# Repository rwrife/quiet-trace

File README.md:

# Quiet Trace

> USB-powered ESP32-S3 ambient sound-level logger for home offices and shared rooms that keeps only privacy-preserving loudness summaries and serves a local history dashboard—never raw audio.

## Overview

Quiet Trace is an open-hardware instrument for understanding *when* a room becomes noisy without installing a recorder or sending microphone data to a cloud service. An ESP32-S3 samples a digital MEMS microphone, calculates bounded-window loudness statistics in memory, discards each audio buffer, and stores only aggregate records such as one-minute equivalent level, peak window, and histogram buckets. A responsive dashboard served on the local network shows live level, timelines, annotations, and portable exports.

Quiet Trace is a practical survey and awareness tool, **not** a certified sound-level meter, occupational exposure instrument, medical device, security monitor, or legal evidence recorder. Displayed units must be labeled uncalibrated until the device has completed a documented reference-meter calibration.

## Motivation

Phone sound-meter apps are convenient but tie up a phone, vary by device, and can create understandable recording concerns. Professional logging meters are expensive and often export through proprietary software. Quiet Trace aims for a small, repairable, visibly non-recording device that can remain on a desk, compare rooms or time periods, and keep the data owner in control.

## Target users

- Remote workers comparing distracting periods before changing their schedule or workspace.
- Households investigating recurring appliance, traffic, or shared-room noise patterns.
- Makers learning digital audio measurement, calibration, embedded aggregation, and privacy-by-design.
- Community rooms and workshops that want a simple local trend display without storing conversations.

## Concrete use cases

1. Put Quiet Trace on a desk, select an existing room label, and watch the current aggregate level.
2. Add a local annotation such as “window opened” or “dishwasher started” and compare the before/after timeline.
3. Move the device to another room and run the same timed survey profile.
4. Export versioned CSV/JSON summaries for a spreadsheet, then delete selected sessions from the device.
5. Demonstrate privacy by inspecting the firmware/data schema: no waveform, encoded audio, transcript, or frequency reconstruction data is persisted or sent.

## Intended workflow

1. Connect Quiet Trace to a certified USB 5 V supply or computer.
2. On first setup, hold the physical setup button to open a time-limited local setup session.
3. Join the temporary device network or use USB serial, set a device name/time source, and optionally provide local Wi-Fi credentials.
4. Open the device-hosted dashboard from a phone or computer on the same network.
5. Choose a room/session label and start logging. The LED communicates recording-*statistics* state without relying on color alone.
6. Review live and historical aggregates; annotate, export, back up, or erase them locally.
7. If calibrated readings are needed, follow the reference-meter procedure and retain the calibration date and offset with every export.

If Wi-Fi is unavailable, logging and physical status remain functional; USB serial supports configuration and data export. No internet service or account is required.

## MVP features

- ESP32-S3 controller, digital I2S/PDM MEMS microphone, status LED, setup/mark button, USB power/data, and test points on an editable KiCad carrier board.
- Fixed-size in-memory sample buffers, documented weighting/aggregation math, and irreversible raw-sample discard.
- One-minute summary records with monotonic sequence, wall-clock quality flag, average/equivalent level, bounded peak, and histogram buckets.
- Explicit calibration state: uncalibrated by default; single-point offset procedure against a reference meter.
- Local flash ring buffer with wear-aware commits and export-before-erase controls.
- Device-hosted responsive web dashboard for setup, live status, history, annotations, CSV/JSON export, backup/restore, retention, and deletion.
- Local-only authenticated API and time-limited physical-presence setup mode.
- Repeatable firmware/web builds, simulation or hardware-abstraction tests, ERC/DRC evidence, bring-up measurements, and assembly/fabrication documentation.

## Non-goals

- Persisting or streaming raw audio, audio clips, spectra, voice activity, speech, transcripts, or speaker identity.
- Certified IEC/ANSI sound-level measurements, occupational dose, hearing-risk advice, diagnosis, treatment, emergency alerts, or regulatory compliance.
- Remote surveillance, cloud dashboards, accounts, analytics, advertisements, or subscription services.
- Automatic identification of a sound source.
- Battery charging in the MVP; operation is USB 5 V SELV only.

## Privacy, permissions, and data storage

Raw microphone samples exist only in bounded RAM buffers required for calculation and are overwritten after each window. The device must never write or transmit samples, recordings, transcripts, or reconstructable spectral data. Stored records contain aggregates, device/session metadata, user-entered annotations, calibration metadata, and timestamps. Data stays in on-device flash and the browser’s local storage unless the user explicitly downloads an export.

The dashboard requires local-network access. Wi-Fi credentials are stored only on the device, must be erasable by a physical reset flow, and are never included in ordinary exports. Setup credentials/tokens must not be hard-coded. No microphone permission is requested from the phone or computer because the device owns the sensor. Optional browser file access is user-initiated for backup restore only.

## Hardware direction

Revision A selects an Espressif `ESP32-S3-WROOM-1-N8R8` module and TDK InvenSense `ICS-43434` I²S microphone, with USB-C 5 V power/protection, non-color-only LED status, physical RESET and SETUP/MARK controls, recovery header, and test access. Exact selected parts, pin/package checks, acoustic constraints, the LDO thermal bound, and point-in-time sourcing evidence are documented in [hardware/parts-selection.md](hardware/parts-selection.md). Stock, prices, and formal lifecycle status still require a pre-order procurement check.

Current editable sources are:

```text
hardware/kicad/quiet-trace.kicad_pro
hardware/kicad/quiet-trace.kicad_sch
hardware/kicad/quiet-trace.kicad_pcb
```

PDFs and renders may supplement these files but will never replace them. Final BOM data lives in KiCad schematic symbol properties (`Manufacturer`, `MPN`, supplier fields, and notes) and is exported to tracked [`bom/bom.csv`](bom/bom.csv). `bom/preliminary-bom.csv` remains planning input only.

Prototype planning target: **USD 35–60**, including electronics, simple enclosure, cable, and ordinary fasteners but excluding a phone/computer, tools, and a reference sound meter. This is a target rather than a live quote; the tracked BOM preserves `TBD` wherever current unit pricing was not actually observed, and all availability must be rechecked before ordering.

## Safety limits

- USB 5 V SELV only; no mains wiring, battery charging, or control of safety-critical equipment.
- Use a certified USB supply and intact cable.
- Indoor, dry-location prototype; not weatherproof.
- Enclosure must prevent conductive debris contact while preserving the microphone’s specified acoustic path.
- Results are informational and unfit for hearing-safety, workplace compliance, tenancy disputes, law enforcement, or emergency decisions.

## Current status and milestones

**Status: issue-5 dashboard/protocol slice is merged; issue-6 physical integration evidence is in progress.** The repository now contains architecture/privacy/metric contracts, selected schematic/BOM, PCB/mechanical draft, host-tested firmware domain contracts, and the merged local dashboard implementation with typed aggregate protocol fixtures. Issue #6 assembly/bring-up/calibration/troubleshooting guides are published, but real bench measurements and end-to-end physical evidence are still required before any calibrated claim. No certification, safety, legal, or bench-calibrated claim is made.

1. Freeze measurable requirements and privacy threat model.
2. Validate controller/microphone/protection choices from manufacturer datasheets.
3. Create the real KiCad schematic and schematic-backed BOM; pass ERC.
4. Build the aggregation firmware and local dashboard against synthetic fixtures.
5. Lay out the PCB; pass DRC and KiCad analysis.
6. Integrate and bring up a prototype with documented measurements and calibration limits.
7. Publish assembly instructions and inspected fabrication/release outputs.

See [PLAN.md](PLAN.md), [hardware/requirements.md](hardware/requirements.md), and the GitHub issue backlog.

Issue-#6 integration documents:
- [Assembly guide](docs/integration/assembly-guide.md)
- [Bring-up checklist](docs/integration/bring-up-checklist.md)
- [Calibration/reference comparison procedure](docs/integration/calibration-reference-comparison.md)
- [Troubleshooting guide](docs/integration/troubleshooting.md)
- [Bench evidence log template](docs/integration/bench-log-template.md)

## Development quickstart

Pinned versions and setup details are in [docs/toolchains.md](docs/toolchains.md).

```bash
# Dashboard: exact lockfile, static checks, tests, and production bundle
cd app
npm ci
npm run format:check
npm run lint
npm run typecheck
npm run test:run
npm run build

# Host-testable firmware domain contract
cd ..
cmake -S firmware/host_tests -B /tmp/quiet-trace-host-tests \
  -DCMAKE_BUILD_TYPE=Release
cmake --build /tmp/quiet-trace-host-tests --parallel
ctest --test-dir /tmp/quiet-trace-host-tests --output-on-failure

# ESP-IDF v6.1 target scaffold (after exporting the pinned IDF environment)
cd firmware
idf.py set-target esp32s3
idf.py build
```

The dashboard’s synthetic view is opt-in at `/?fixture=1` and visibly marked as fixture-only. The default route does not fabricate sensor data. Target flashing, microphone behavior, calibration, and bench results remain unverified until the exact hardware is selected and present.

## Licensing plan

The initial documentation/software scaffold is MIT licensed. Before hardware source release, the project will add an explicit open-hardware license (planned CERN-OHL-S-2.0) and document boundaries for firmware, web app, documentation, and third-party assets.

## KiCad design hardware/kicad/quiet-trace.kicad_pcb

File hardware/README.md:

# Quiet Trace hardware

## System block description

```text
USB-C 5 V SELV
      │
      ├─ input protection / regulated module rail / test points
      │
      ▼
ESP32-S3 module ── digital audio ── MEMS microphone + acoustic port
      │
      ├─ setup/mark button
      ├─ status LED with blink-pattern redundancy
      ├─ native USB / serial recovery
      └─ Wi-Fi local dashboard
```

The first revision is a carrier around an Espressif ESP32-S3 module rather than a chip-down RF design. It should remain hand-assemblable, expose recovery and measurement points, and keep the module antenna region outside copper/enclosure obstructions.

## Controller choice

Revision A selects `ESP32-S3-WROOM-1-N8R8` after comparison with `ESP32-S3-MINI-1-N8`. The WROOM variant provides 8 MB flash and 8 MB PSRAM, native USB on GPIO19/GPIO20, official KiCad library support, and a less dense assembly footprint. See [parts-selection.md](parts-selection.md) for datasheet citations, sourcing limits, and the +65 °C normal operating limit of the R8 PSRAM variant.

## Interfaces

- Digital microphone: TDK InvenSense `ICS-43434`, 24-bit I²S; firmware clocks must stay within the selected datasheet operating bands.
- USB: 5 V power plus flashing, logs, setup, recovery, and aggregate export.
- Wi-Fi: local HTTP/JSON/SSE only; internet not required.
- Human input: one setup/mark button with short/long press semantics.
- Human output: LED patterns that remain understandable without color perception.
- Debug/test: ground, input/regulated rail, reset/boot, audio clocks/data, and spare serial/SWD-style module test access as supported.

## Power plan

USB 5 V SELV only. Revision A uses a 500 mA-hold resettable fuse, VBUS TVS, USB data ESD array, and a 600 mA AP2112K 3.3 V LDO. The LDO's current rating is not continuous thermal capacity: [parts-selection.md](parts-selection.md) records the static thermal bounds and required worst-case current/temperature bring-up measurement. No battery, charging circuit, mains interface, PoE, or external actuator is in MVP. Use a certified USB supply and intact cable.

## Revision-A PCB and enclosure

Revision A uses an 80 × 52 mm two-layer carrier with four M3 holes. The USB-C receptacle is on the left edge, the WROOM module antenna overhangs the top edge, the bottom-port microphone is aligned to its footprint's 0.5 mm NPTH, and reset/setup/status controls remain accessible from the top. The board has labeled test points for protected 5 V, 3V3, GND, USB D+/D−, microphone clocks/data, EN, and BOOT0.

`hardware/mechanical/quiet-trace-enclosure.scad` is an editable 88 × 60 × 24 mm two-part enclosure model. It aligns standoffs, USB access, button holes, status window, and microphone opening to PCB coordinates and opens with common M3 hardware. The model is dimensional/static evidence only: it has not been printed, assembled, RF-tested, thermally tested, or acoustically characterized.

## Safety limits

- Indoor dry-location prototype, USB 5 V SELV only.
- No claim of ingress protection, acoustic certification, hearing safety, regulatory compliance, surveillance, or emergency monitoring.
- Keep conductive debris away and maintain the module antenna/microphone keepouts.
- Raw audio must never be persisted or transmitted.

## Expected KiCad deliverables

Current editable paths:

```text
hardware/kicad/quiet-trace.kicad_pro
hardware/kicad/quiet-trace.kicad_sch
hardware/kicad/quiet-trace.kicad_pcb
hardware/kicad/quiet-trace.kicad_dru
hardware/mechanical/quiet-trace-enclosure.scad
```

The design must include power/protection, controller/module sockets or pads, microphone interface, controls, status, programming/recovery, test points, mounting, antenna/acoustic keepouts, and labeled connectors. Completion requires actual ERC/DRC output with every exception resolved or documented. Renders and schematic PDFs supplement but do not replace editable KiCad source.

Layout implementation: the official ESP32-S3-WROOM-1 footprint's embedded F.Cu/B.Cu antenna rule area spans the radiating edge and forbids tracks, vias, pads, pours, and footprints. U4 retains the footprint's 0.5 mm acoustic NPTH; board-level front/back acoustic rule areas prevent pours/vias beneath it and prevent back-side tracks. U3 sits directly behind J1; R3/R4 terminate near U1; C1/C2 flank U2; C3/C4 sit at the module rail entry; C5 is adjacent to U4. J2 remains DNP by default.

The continuous-ground strategy uses filled GND zones on F.Cu and B.Cu, clipped by antenna, mounting, and microphone rule areas. Power nets are widened after routing (`VBUS_RAW`/`USB_5V` 0.4 mm, `+3V3` 0.5 mm); USB and I²S are 0.25 mm. The custom rule file enforces these widths/clearances. These dimensions support a conservative two-layer prototype; they do not constitute controlled-impedance or EMC-compliance evidence.

### Assembly/fabrication constraints

- Two-layer 1.6 mm FR-4, 1 oz copper planning basis; minimum track/clearance 0.2 mm, minimum copper-to-edge 0.5 mm.
- Keep all copper, components, metal hardware, conductive coating, and cabling out of the WROOM antenna rule area.
- Do not apply solder paste, wash fluid, mesh, foam, adhesive, or debris to the ICS-43434 sound hole. Align any enclosure port before assembly.
- Fit U3 directly behind J1 and inspect USB-C/ESD orientation before power. D2 is bidirectional; D1 polarity and all IC/module pin-1 marks are present in the library footprints/silkscreen.
- J2 is DNP unless needed for development. Preserve access to U2 and TP1/TP2/TP3 for issue-#6 rail/current/temperature measurements.
- No Gerber/CPL/release package is checked in at this stage; issue #7 owns final fabrication export and inspection.

The reproducible issue-#2 ERC/netlist/BOM evidence is recorded in [`docs/verification/issue-2-schematic.md`](../docs/verification/issue-2-schematic.md). Issue-#3 DRC, routing, cross-analysis, EMC/thermal triage, and mechanical evidence is recorded in [`docs/verification/issue-3-pcb-mechanical.md`](../docs/verification/issue-3-pcb-mechanical.md). Issue-#6 integration docs are in [`docs/integration/assembly-guide.md`](../docs/integration/assembly-guide.md), [`docs/integration/bring-up-checklist.md`](../docs/integration/bring-up-checklist.md), [`docs/integration/calibration-reference-comparison.md`](../docs/integration/calibration-reference-comparison.md), and [`docs/integration/troubleshooting.md`](../docs/integration/troubleshooting.md), with run-time capture template [`docs/integration/bench-log-template.md`](../docs/integration/bench-log-template.md). After exporting the KiCad XML netlist, run `python3 hardware/kicad/verify_netlist.py hardware/kicad/quiet-trace.xml` and `python3 hardware/kicad/verify_pcb.py hardware/kicad/quiet-trace.xml hardware/kicad/quiet-trace.kicad_pcb`.

Final Manufacturer/MPN/supplier data belongs in schematic symbol properties and is exported to `bom/bom.csv`; `bom/preliminary-bom.csv` is not the source of truth.

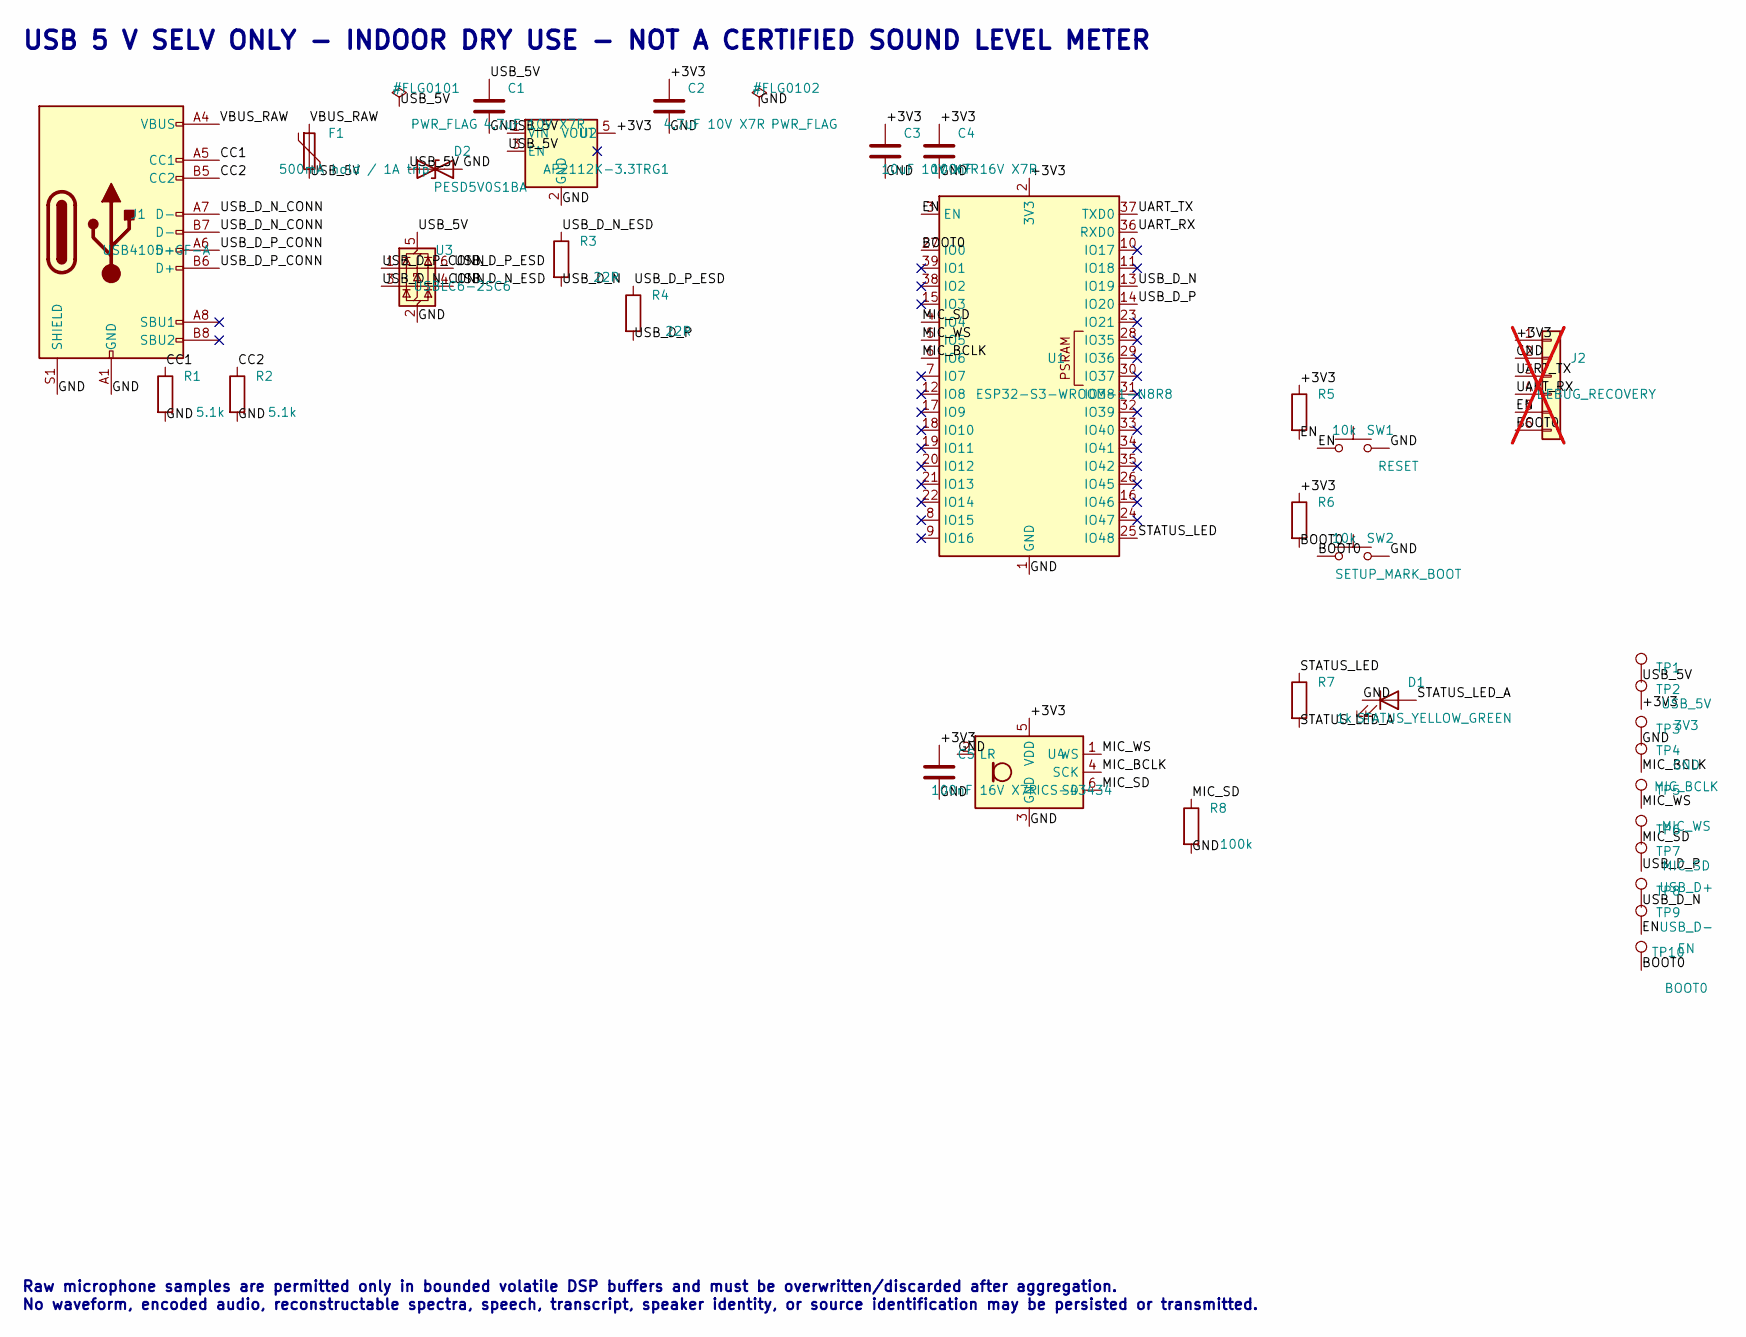
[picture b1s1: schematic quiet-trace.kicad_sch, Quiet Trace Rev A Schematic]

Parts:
C1, C2: 4.7uF 10V X7R; C_0603_1608Metric; MPN TCC0603X7R475K100CT
C3: 10uF 10V X7R; C_0805_2012Metric; MPN GRM21BR71A106KE51L
C4, C5: 100nF 16V X7R; C_0603_1608Metric; MPN GRM188R71C104KA01D
D1: STATUS_YELLOW_GREEN; LED_0805_2012Metric; MPN LTST-C170KGKT
D2: PESD5V0S1BA; D_SOD-323; MPN PESD5V0S1BA,115
F1: 500mA hold / 1A trip; Fuse_1206_3216Metric; MPN BSMD1206-050-16V
J1: USB4105-GF-A; USB_C_Receptacle_GCT_USB4105-xx-A_16P_TopMnt_Horizontal; MPN USB4105-GF-A
J2: DEBUG_RECOVERY; PinHeader_1x06_P2.54mm_Vertical; MPN M20-9990645; not fitted
R1, R2: 5.1k; R_0603_1608Metric; MPN 0603WAF5101T5E
R3, R4: 22R; R_0603_1608Metric; MPN 0603WAF220JT5E
R5, R6: 10k; R_0603_1608Metric; MPN 0603WAF1002T5E
R7: 1k; R_0603_1608Metric; MPN 0603WAF1001T5E
R8: 100k; R_0603_1608Metric; MPN 0603WAF1003T5E
SW1: RESET; SW_Push_1P1T_NO_CK_KMR2; MPN KMR221GLFS
SW2: SETUP_MARK_BOOT; SW_Push_1P1T_NO_CK_KMR2; MPN KMR221GLFS
TP1: USB_5V; TestPoint_Pad_D1.5mm; MPN N/A
TP2: 3V3; TestPoint_Pad_D1.5mm; MPN N/A
TP3: GND; TestPoint_Pad_D1.5mm; MPN N/A
TP4: MIC_BCLK; TestPoint_Pad_D1.5mm; MPN N/A
TP5: MIC_WS; TestPoint_Pad_D1.5mm; MPN N/A
TP6: MIC_SD; TestPoint_Pad_D1.5mm; MPN N/A
TP7: USB_D+; TestPoint_Pad_D1.5mm; MPN N/A
TP8: USB_D-; TestPoint_Pad_D1.5mm; MPN N/A
TP9: EN; TestPoint_Pad_D1.5mm; MPN N/A
TP10: BOOT0; TestPoint_Pad_D1.5mm; MPN N/A
U1: ESP32-S3-WROOM-1-N8R8; ESP32-S3-WROOM-1; MPN ESP32-S3-WROOM-1-N8R8
U2: AP2112K-3.3TRG1; SOT-23-5; MPN AP2112K-3.3TRG1
U3: USBLC6-2SC6; SOT-23-6; MPN USBLC6-2SC6
U4: ICS-43434; InvenSense_ICS-43434-6_3.5x2.65mm; MPN ICS-43434

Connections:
+3V3: C2.1, C3.1, C4.1, C5.1, J2.1, R5.1, R6.1, TP2.1, U1.2 (3V3), U2.5 (VOUT), U4.5 (VDD)
BOOT0: J2.6, R6.2, SW2.1, TP10.1, U1.27 (IO0)
CC1: J1.A5 (CC1), R1.1
CC2: J1.B5 (CC2), R2.1
EN: J2.5, R5.2, SW1.1, TP9.1, U1.3 (EN)
GND: C1.2, C2.2, C3.2, C4.2, C5.2, D1.1 (K), D2.2 (A2), J1.A1 (GND), J1.A12 (GND), J1.B1 (GND), J1.B12 (GND), J1.S1 (SHIELD), J2.2, R1.2, R2.2, R8.2, SW1.2, SW2.2, TP3.1, U1.1 (GND), U1.40 (GND), U1.41 (GND), U2.2 (GND), U3.2 (GND), U4.2 (LR), U4.3 (GND)
MIC_BCLK: TP4.1, U1.6 (IO6), U4.4 (SCK)
MIC_SD: R8.1, TP6.1, U1.4 (IO4), U4.6 (SD)
MIC_WS: TP5.1, U1.5 (IO5), U4.1 (WS)
STATUS_LED: R7.1, U1.25 (IO48)
STATUS_LED_A: D1.2 (A), R7.2
UART_RX: J2.4, U1.36 (RXD0)
UART_TX: J2.3, U1.37 (TXD0)
USB_5V: C1.1, D2.1 (A1), F1.2, TP1.1, U2.1 (VIN), U2.3 (EN), U3.5 (VBUS)
USB_D_N: R3.2, TP8.1, U1.13 (IO19)
USB_D_N_CONN: J1.A7 (D-), J1.B7 (D-), U3.3 (I/O2)
USB_D_N_ESD: R3.1, U3.4 (I/O2)
USB_D_P: R4.2, TP7.1, U1.14 (IO20)
USB_D_P_CONN: J1.A6 (D+), J1.B6 (D+), U3.1 (I/O1)
USB_D_P_ESD: R4.1, U3.6 (I/O1)
VBUS_RAW: F1.1, J1.A4 (VBUS), J1.A9 (VBUS), J1.B4 (VBUS), J1.B9 (VBUS)

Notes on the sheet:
USB 5 V SELV ONLY - INDOOR DRY USE - NOT A CERTIFIED SOUND LEVEL METER
Raw microphone samples are permitted only in bounded volatile DSP buffers and must be overwritten/discarded after aggregation.
No waveform, encoded audio, reconstructable spectra, speech, transcript, speaker identity, or source identification may be persisted or transmitted.

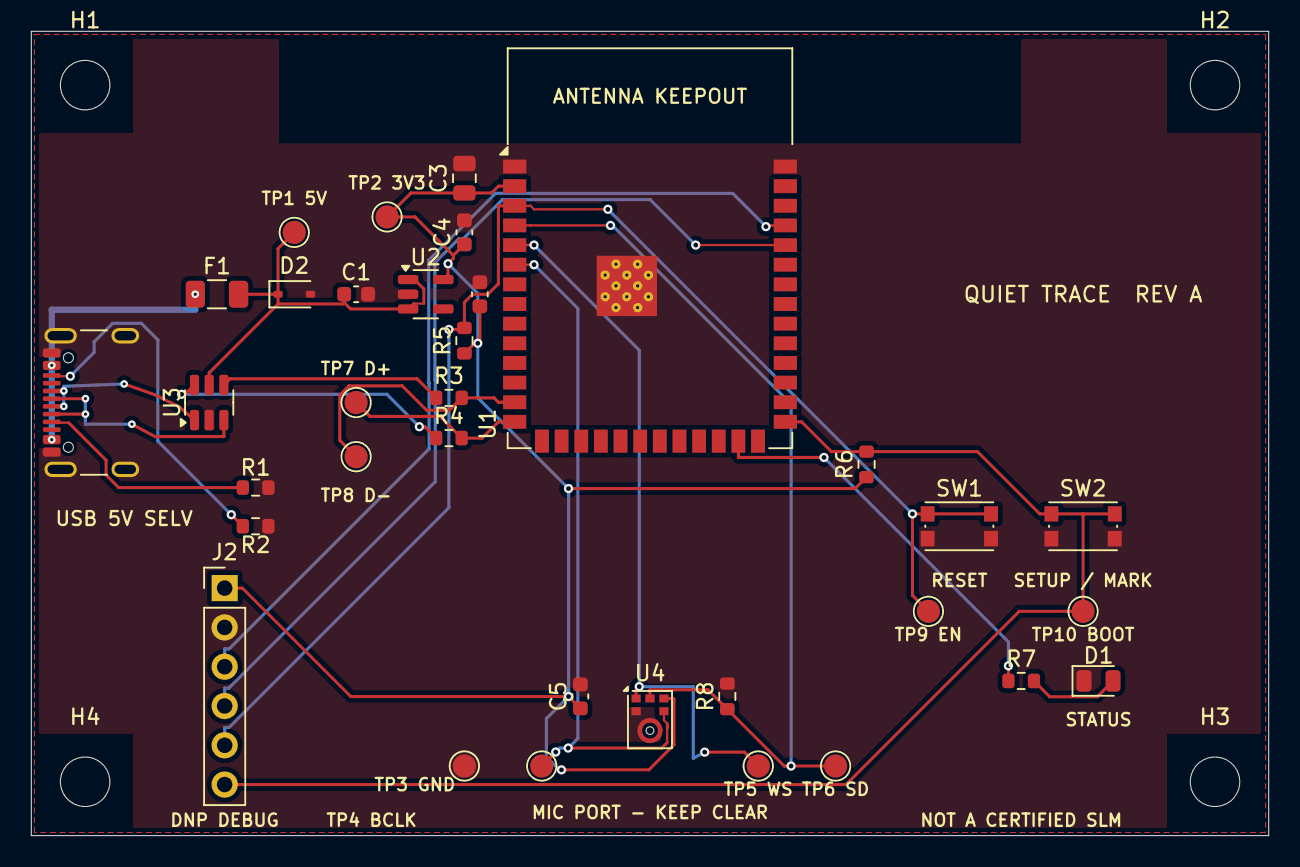
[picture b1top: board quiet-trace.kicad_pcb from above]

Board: 2 copper layers, 80.0 x 52.0 mm, 38 parts (0 on the bottom side), 21 nets.

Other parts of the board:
H1, H2, H3, H4: MountingHole_3.2mm_M3

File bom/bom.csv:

Reference,Qty,Value / Description,Footprint / Package,Manufacturer,MPN,Supplier / Source,Supplier PN,Estimated Unit Cost USD,Availability / Price Check,Datasheet,DNP,Notes
"C1,C2",2,4.7uF 10V X7R,Capacitor_SMD:C_0603_1608Metric,CCTC,TCC0603X7R475K100CT,LCSC,C18185770,TBD,"LCSC checked 2026-08-30: 445,583 stock",https://jlcpcb.com/partdetail/CCTC-TCC0603X7R475K100CT/C18185770,no,LDO input capacitor; account for DC-bias derating.; LDO output capacitor; place at VOUT/GND.
C3,1,10uF 10V X7R,Capacitor_SMD:C_0805_2012Metric,Murata Electronics,GRM21BR71A106KE51L,LCSC,C86038,TBD,"LCSC checked 2026-08-30: 10,453 stock",https://www.murata.com/en-us/products/productdetail?partno=G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,no,3V3 bulk near ESP32 module; 0805 footprint for DC-bias margin.
"C4,C5",2,100nF 16V X7R,Capacitor_SMD:C_0603_1608Metric,Murata Electronics,GRM188R71C104KA01D,LCSC,C45000,TBD,"LCSC checked 2026-08-30: 3,848 stock",https://www.murata.com/en-us/products/productdetail?partno=G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,no,ESP32 local high-frequency decoupling.; Microphone bypass; place adjacent to U4 pin 5 and GND without vias.
D1,1,STATUS_YELLOW_GREEN,LED_SMD:LED_0805_2012Metric,Lite-On,LTST-C170KGKT,LCSC,C98221,0.0251,"LCSC checked 2026-08-30: 15,021 stock; USD 0.0251 @1",https://optoelectronics.liteon.com/upload/download/DS22-2000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,no,"Status meaning must use blink pattern/timing, never color alone."
D2,1,PESD5V0S1BA,Diode_SMD:D_SOD-323,Nexperia,"PESD5V0S1BA,115",LCSC,C19224,0.0422,"LCSC checked 2026-08-30: 4,810 stock; USD 0.0422 @1",https://assets.nexperia.com/documents/data-sheet/PESD5V0S1BA.pdf,no,Bidirectional 5 V TVS on protected USB_5V rail; not a mains surge device.
F1,1,500mA hold / 1A trip,Fuse:Fuse_1206_3216Metric,BHFUSE,BSMD1206-050-16V,LCSC,C883124,0.0518,"LCSC checked 2026-08-30: 63,238 stock; USD 0.0518 @1",https://cdn.semikey.com/upload/pdfs/69/4f/694fbc200bff214208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,no,"USB VBUS resettable protection; 0.5 A hold, 1 A trip, 16 V."
J1,1,USB4105-GF-A,Connector_USB:USB_C_Receptacle_GCT_USB4105-xx-A_16P_TopMnt_Horizontal,GCT,USB4105-GF-A,LCSC,C3020560,1.0319,"LCSC checked 2026-08-30: 11,505 stock; USD 1.0319 @1",https://gct.co/files/drawings/usb4105.pdf,no,USB 2.0 device receptacle; 5.1 kOhm Rd required on CC1/CC2; shell to GND.
J2,1,DEBUG_RECOVERY,Connector_PinHeader_2.54mm:PinHeader_1x06_P2.54mm_Vertical,Harwin,M20-9990645,DigiKey,952-2267-ND,TBD,Supplier stock not API-verified on 2026-08-30; DNP by default,https://cdn.harwin.com/pdfs/M20-999.pdf,yes,"DNP debug/recovery header: 3V3, GND, UART_TX, UART_RX, EN, BOOT0. Populate only for development."
"R1,R2",2,5.1k,Resistor_SMD:R_0603_1608Metric,UniOhm,0603WAF5101T5E,LCSC,C23186,TBD,"LCSC checked 2026-08-30: 3,775,920 stock",https://www.uniroyal.com.tw/upload/media/product/Thick_Film_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,no,USB-C CC1 Rd to GND.; USB-C CC2 Rd to GND.
"R3,R4",2,22R,Resistor_SMD:R_0603_1608Metric,UniOhm,0603WAF220JT5E,LCSC,C23345,TBD,"LCSC checked 2026-08-30: 2,657,294 stock",https://www.uniroyal.com.tw/upload/media/product/Thick_Film_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,no,USB D- source termination; place near module.; USB D+ source termination; place near module.
"R5,R6",2,10k,Resistor_SMD:R_0603_1608Metric,UniOhm,0603WAF1002T5E,LCSC,C25804,TBD,"LCSC checked 2026-08-30: 1,709,000 stock",https://www.uniroyal.com.tw/upload/media/product/Thick_Film_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,no,EN pull-up to 3V3.; GPIO0 boot pull-up to 3V3.
R7,1,1k,Resistor_SMD:R_0603_1608Metric,UniOhm,0603WAF1001T5E,LCSC,C21190,TBD,"LCSC checked 2026-08-30: 8,013,731 stock",https://www.uniroyal.com.tw/upload/media/product/Thick_Film_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,no,Status LED current limit.
R8,1,100k,Resistor_SMD:R_0603_1608Metric,UniOhm,0603WAF1003T5E,LCSC,C25803,TBD,"LCSC checked 2026-08-30: 7,990,119 stock",https://www.uniroyal.com.tw/upload/media/product/Thick_Film_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,no,I2S SD pull-down required while microphone output is tri-stated.
SW1,1,RESET,Button_Switch_SMD:SW_Push_1P1T_NO_CK_KMR2,C&K,KMR221GLFS,LCSC,C72443,0.6508,"LCSC checked 2026-08-30: 23,634 stock; USD 0.6508 @1",https://www.ckswitches.com/media/1479/kmr2.pdf,no,Momentary active-low reset button.
SW2,1,SETUP_MARK_BOOT,Button_Switch_SMD:SW_Push_1P1T_NO_CK_KMR2,C&K,KMR221GLFS,LCSC,C72443,0.6508,"LCSC checked 2026-08-30: 23,634 stock; USD 0.6508 @1",https://www.ckswitches.com/media/1479/kmr2.pdf,no,"GPIO0 active-low; boot strap during reset, setup/mark input after boot. Firmware must debounce and distinguish physical-presence holds."
TP1,1,USB_5V,TestPoint:TestPoint_Pad_D1.5mm,PCB feature,N/A,N/A,N/A,N/A,Fabricated as exposed plated pad,~,no,Protected USB VBUS after F1; excluded from purchased BOM.
TP2,1,3V3,TestPoint:TestPoint_Pad_D1.5mm,PCB feature,N/A,N/A,N/A,N/A,Fabricated as exposed plated pad,~,no,Regulated 3.3 V; excluded from purchased BOM.
TP3,1,GND,TestPoint:TestPoint_Pad_D1.5mm,PCB feature,N/A,N/A,N/A,N/A,Fabricated as exposed plated pad,~,no,Ground; excluded from purchased BOM.
TP4,1,MIC_BCLK,TestPoint:TestPoint_Pad_D1.5mm,PCB feature,N/A,N/A,N/A,N/A,Fabricated as exposed plated pad,~,no,I2S bit clock; excluded from purchased BOM.
TP5,1,MIC_WS,TestPoint:TestPoint_Pad_D1.5mm,PCB feature,N/A,N/A,N/A,N/A,Fabricated as exposed plated pad,~,no,I2S word select; excluded from purchased BOM.
TP6,1,MIC_SD,TestPoint:TestPoint_Pad_D1.5mm,PCB feature,N/A,N/A,N/A,N/A,Fabricated as exposed plated pad,~,no,I2S microphone data; excluded from purchased BOM.
TP7,1,USB_D+,TestPoint:TestPoint_Pad_D1.5mm,PCB feature,N/A,N/A,N/A,N/A,Fabricated as exposed plated pad,~,no,USB device D+; excluded from purchased BOM.
TP8,1,USB_D-,TestPoint:TestPoint_Pad_D1.5mm,PCB feature,N/A,N/A,N/A,N/A,Fabricated as exposed plated pad,~,no,USB device D-; excluded from purchased BOM.
TP9,1,EN,TestPoint:TestPoint_Pad_D1.5mm,PCB feature,N/A,N/A,N/A,N/A,Fabricated as exposed plated pad,~,no,ESP32 enable/reset; excluded from purchased BOM.
TP10,1,BOOT0,TestPoint:TestPoint_Pad_D1.5mm,PCB feature,N/A,N/A,N/A,N/A,Fabricated as exposed plated pad,~,no,GPIO0 boot/setup-mark; excluded from purchased BOM.
U1,1,ESP32-S3-WROOM-1-N8R8,RF_Module:ESP32-S3-WROOM-1,Espressif Systems,ESP32-S3-WROOM-1-N8R8,LCSC,C2913201,4.9831,"LCSC checked 2026-08-30: 6,547 stock; USD 4.9831 @1",https://www.espressif.com/sites/default/files/documentation/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,no,8 MB flash + 8 MB PSRAM; 3.0-3.6 V; supply capable of >=500 mA; preserve module antenna keepout per datasheet/hardware design guide.
U2,1,AP2112K-3.3TRG1,Package_TO_SOT_SMD:SOT-23-5,Diodes Incorporated,AP2112K-3.3TRG1,LCSC,C51118,0.1577,"LCSC checked 2026-08-30: 79,480 stock; USD 0.1577 @1",https://www.diodes.com/assets/Datasheets/AP2112.pdf,no,600 mA fixed 3.3 V LDO; EN tied to protected USB_5V; validate thermal margin during bring-up.
U3,1,USBLC6-2SC6,Package_TO_SOT_SMD:SOT-23-6,STMicroelectronics,USBLC6-2SC6,LCSC,C7519,TBD,LCSC exact ST catalog mapping checked 2026-08-31; live stock/price unavailable from accessible endpoint; recheck before ordering.,https://www.st.com/resource/en/datasheet/usblc6-2.pdf,no,Place directly behind J1; route D+/D- straight through matched I/O pairs with shortest ESD ground return.
U4,1,ICS-43434,Sensor_Audio:InvenSense_ICS-43434-6_3.5x2.65mm,TDK InvenSense,ICS-43434,LCSC,C5656610,6.7694,"LCSC checked 2026-08-30: 3,332 stock; USD 6.7694 @1",https://product.tdk.com/system/files/dam/doc/product/sw_piez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,no,"Bottom-port I2S microphone; 60 Hz-20 kHz, -26 dBFS +/-1 dB, 120 dB SPL AOP. Keep port clear; minimum PCB sound-hole diameter 0.5 mm; no wash ingress."

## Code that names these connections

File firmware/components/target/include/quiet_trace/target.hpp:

#pragma once

#include "quiet_trace/acquisition_pipeline.hpp"
#include "quiet_trace/aggregate_contract.hpp"
#include "quiet_trace/control_plane.hpp"
#include "quiet_trace/record_ring.hpp"

#include <cstdint>
#include <optional>
#include <string>
#include <string_view>
#include <vector>

namespace quiet_trace::target {

// Hardware pin map for revision A (hardware/parts-selection.md pin audit and
// hardware/kicad/quiet-trace.kicad_sch MIC_* nets). This is a design-intent
// constant block, not verified-on-silicon behavior.
inline constexpr int kMicBclkGpio = 4;    // MIC_BCLK (module pin 4 / GPIO4)
inline constexpr int kMicWsGpio = 5;      // MIC_WS (module pin 5 / GPIO5)
inline constexpr int kMicSdGpio = 6;      // MIC_SD (module pin 6 / GPIO6)
inline constexpr int kStatusLedGpio = 48; // GPIO48 -> D1 through R6
inline constexpr int kSetupMarkGpio = 0;  // GPIO0 BOOT/SETUP_MARK (SW2)

// In-memory aggregate retention. The v1 slice keeps one boot session of
// minute records in bounded internal RAM; SPIFFS persistence and its
// power-loss behavior are deferred to physical bring-up (issue #6) because
// the on-flash format has no physical validation yet. 10,080 records is the
// 7-day capacity target from docs/metrics.md.
inline constexpr std::size_t kRingCapacityRecords = 10'080;

inline constexpr std::uint32_t kAcquisitionBlockSamples = 240U;

struct ClockSnapshot {
  ClockQuality quality;
  // Wall-clock epoch ms derived at snapshot time (null when no time source).
  std::optional<std::int64_t> epoch_offset_ms;
};

// Pure classification of clock quality (no hardware state) for host tests.
[[nodiscard]] ClockQuality
classify_clock_quality(bool time_synced, bool host_set_time,
                       bool sync_failed_since_host_set) noexcept;

[[nodiscard]] std::int64_t uptime_us_to_ms(std::int64_t uptime_us) noexcept;

// Parses the strict `YYYY-MM-DDTHH:MM:SSZ` form accepted by the USB
// `time set` command into epoch milliseconds; rejects impossible dates.
[[nodiscard]] std::optional<std::int64_t>
parse_iso8601_utc_ms(std::string_view timestamp) noexcept;

class SystemState {
public:
  SystemState();

  [[nodiscard]] AcquisitionPipeline &pipeline() noexcept;
  [[nodiscard]] AggregateRingStore &store() noexcept;
  [[nodiscard]] SetupAuthorizer &setup() noexcept;
  [[nodiscard]] UsbCommandRouter &router() noexcept;

  // Latches the button state with free-running microseconds at the edge.
  void set_button_held(bool held, std::int64_t now_us) noexcept;
  [[nodiscard]] bool button_held() const noexcept;
  [[nodiscard]] std::uint32_t
  button_hold_us(std::int64_t now_us) const noexcept;
  // True while the button is being held or was released within `window_us`.
  [[nodiscard]] bool
  physical_presence_recent(std::int64_t now_us,
                           std::int64_t window_us) const noexcept;

  void set_reboot_requested() noexcept;
  [[nodiscard]] bool reboot_requested() const noexcept;

  // Credentials held only in volatile RAM for this boot session (v1 slice);
  // `take_wifi_credentials` moves them out for the network task.
  void record_wifi_credentials(std::string ssid, std::string password);
  [[nodiscard]] bool take_wifi_credentials(std::string &ssid,
                                           std::string &password) noexcept;

  void set_host_time(std::int64_t epoch_ms, std::int64_t uptime_us) noexcept;
  void mark_time_synced(std::int64_t epoch_ms, std::int64_t uptime_us) noexcept;
  void mark_time_sync_failed() noexcept;
  [[nodiscard]] ClockSnapshot clock_snapshot(std::int64_t uptime_us) noexcept;

private:
  AcquisitionPipeline pipeline_;
  AggregateRingStore store_{kRingCapacityRecords};
  SetupAuthorizer setup_{};
  UsbCommandRouter router_{&setup_, &store_};

  bool button_held_ = false;
  std::int64_t button_edge_us_ = 0;

  bool reboot_requested_ = false;

  std::string pending_ssid_;
  std::string pending_password_;
  bool wifi_pending_ = false;

  bool time_synced_ = false;
  bool host_set_time_ = false;
  bool sync_failed_since_host_set_ = false;
  std::int64_t host_epoch_ms_ = 0;
  std::int64_t host_uptime_us_ = 0;
  std::int64_t synced_epoch_ms_ = 0;
  std::int64_t synced_uptime_us_ = 0;
};

// JSON/CSV export bodies for the USB `export` command and the HTTP export
// endpoint, rendered from the exported store contents. Aggregate-only.
[[nodiscard]] std::string render_usb_export_json(
    const std::vector<StoredAggregate> &records, ClockQuality clock_quality,
    std::optional<std::int64_t> epoch_offset_ms, std::int64_t uptime_us);
[[nodiscard]] std::string
render_usb_export_csv(const std::vector<StoredAggregate> &records,
                      ClockQuality clock_quality,
                      std::optional<std::int64_t> epoch_offset_ms);

// Console-line dispatch. Extends the shared UsbCommandRouter contract with
// `time set <token> <timestamp>` value application; everything else routes
// to the domain router. Kept free of IDF calls so host tests cover it.
[[nodiscard]] UsbResponse handle_console_line(SystemState &state,
                                              std::string_view line,
                                              std::int64_t now_us,
                                              bool physical_button_confirmed,
                                              std::uint64_t nonce);

// Single production entry point used by app_main(): initializes adapters and
// starts acquisition, aggregation, control, console, LED, and network tasks.
// Returns false when a required driver fails; the LED then runs the error
// pattern. Implemented in the ESP-IDF-only translation unit.
bool start_all();

SystemState &state();

} // namespace quiet_trace::target
